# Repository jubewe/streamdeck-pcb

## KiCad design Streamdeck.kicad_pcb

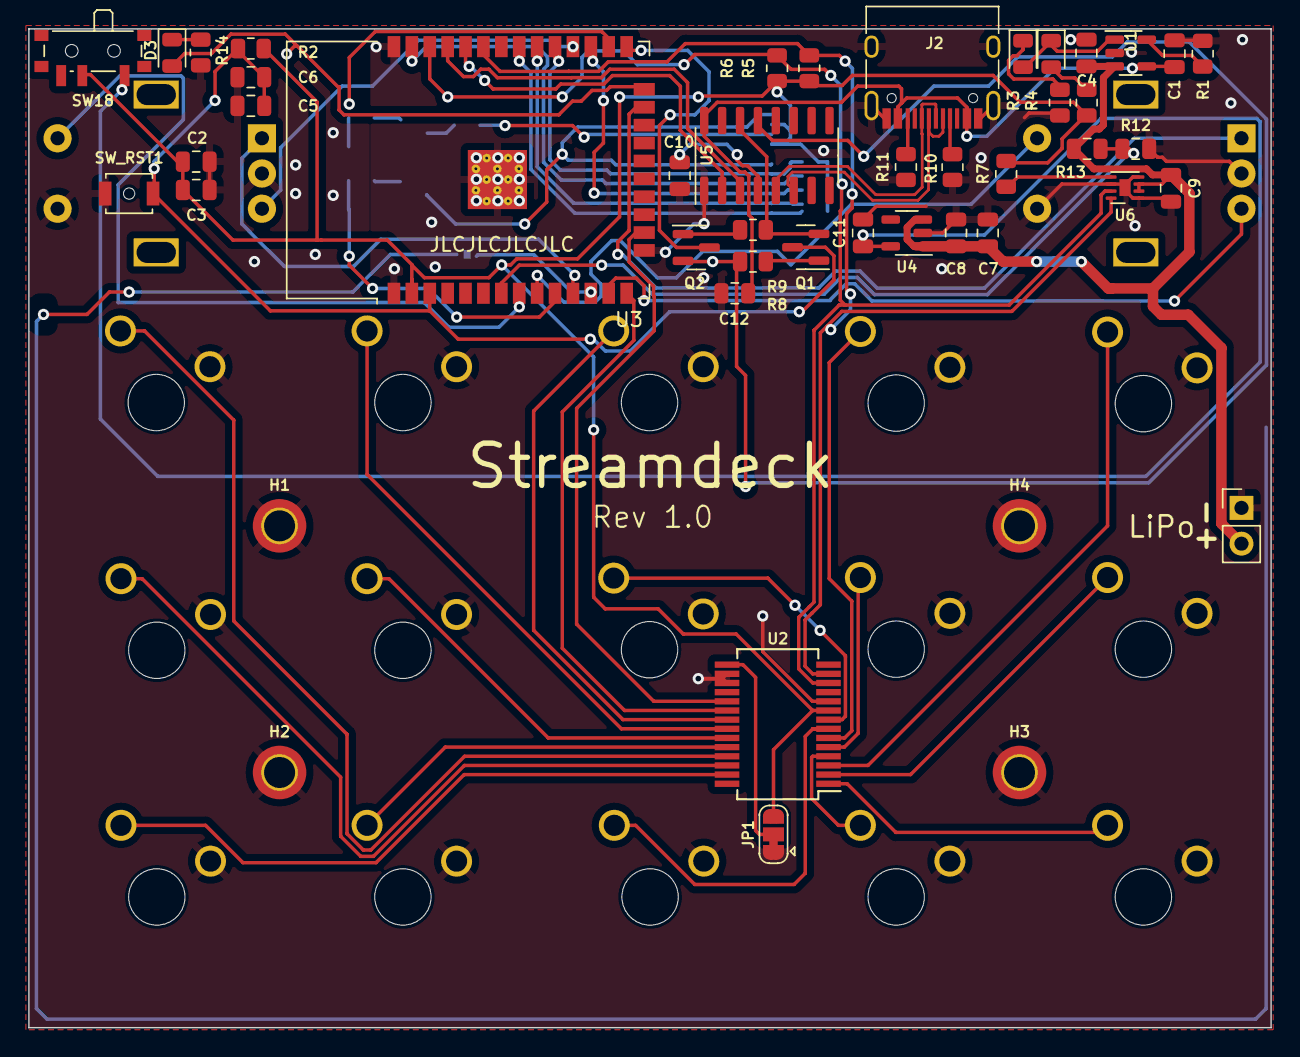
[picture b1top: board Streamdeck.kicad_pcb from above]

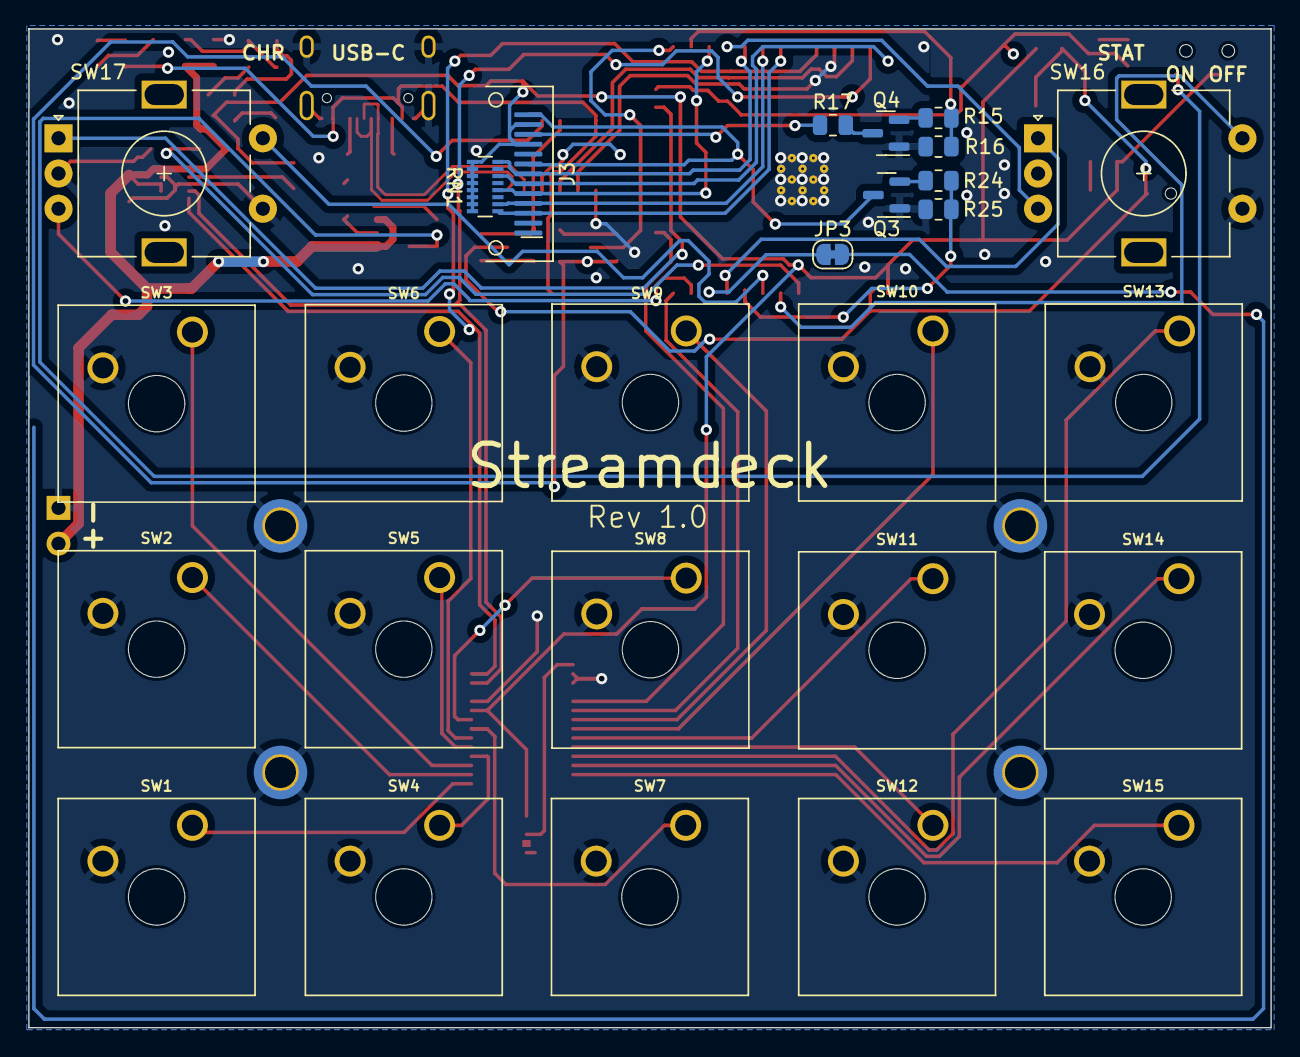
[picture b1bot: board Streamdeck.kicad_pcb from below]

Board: 2 copper layers, 88.1 x 70.9 mm, 73 parts (27 on the bottom side), 65 nets.

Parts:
C1, C2, C4, C7: 10µF; C_0805_2012Metric
C3, C6, C9, C10, C12: 0.1µF; C_0805_2012Metric
C5, C8, C11: 1µF; C_0805_2012Metric
D1: LED_GREEN; LED_0805_2012Metric
D2: LED_RED; LED_0805_2012Metric
D3: LED_BLUE; LED_0805_2012Metric
H1, H2, H3, H4: MountingHole_Pad; MountingHole_2.2mm_M2_DIN965_Pad_TopBottom
J1: Conn_01x02_Socket; PinHeader_1x02_P2.54mm_Vertical
J2: XUNPU_TYPEC-304J-BCP16; XUNPU TYPEC-304J-BCP16
J3: Conn_01x13_Pin; ST7789 LCD TFT
JP1: Jumper_3_Bridged12; SolderJumper-3_P1.3mm_Bridged12_RoundedPad1.0x1.5mm
JP3: Jumper_2_Bridged; SolderJumper-2_P1.3mm_Bridged_RoundedPad1.0x1.5mm
Q1, Q2: BC817; SOT-23
Q3, Q4: S8050; SOT-23
R1, R3, R4, R14: 2k; R_0805_2012Metric
R2, R8, R9: 10k; R_0805_2012Metric
R5, R6: 2k2; R_0805_2012Metric
R7: 4.7k; R_0805_2012Metric
R10, R11: 5.1k; R_0805_2012Metric
R12, R13: R; C_0805_2012Metric
R15, R24: 1k; R_0805_2012Metric
R16, R25: 100k; R_0805_2012Metric
R17: 36; R_0805_2012Metric
RN1: R_Pack08; R_Array_Convex_8x0602
SW1, SW2, SW3, SW4, SW5, SW6, SW7, SW8, SW9, SW10, SW11, SW12, SW13, SW14, SW15: SW; SW_Cherry_MX_1.00u_Plate_Custom
SW16, SW17: RotaryEncoder_Switch; RotaryEncoder_Alps_EC11E-Switch_Vertical_H20mm
SW18: SW_SPST; SW_SPDT_PCM12
SW_RST1: SW_RESET; SW_SPST_B3U-1000P-B
U1: MCP73831-2-OT; SOT-23-5
U2: MCP23017_SO; SSOP-28_5.3x10.2mm_P0.65mm
U3: ESP32-WROOM-32
U4: XC6220B331MR; SOT-23-5
U5: CH340C; SOIC-16_3.9x9.9mm_P1.27mm
U6: MAX17048; TDFN-8-1EP_2x2mm_P0.5mm_EP0.8x1.2mm

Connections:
+3.3V: C2.1, C3.1, J3.10, J3.12, JP1.3 (B), R2.2, R4.2, R5.1, R6.1, R7.2, RN1.9 (R8.2), RN1.10 (R7.2), RN1.11 (R6.2), RN1.12 (R5.2), RN1.13 (R4.2), RN1.14 (R3.2), RN1.15 (R2.2), RN1.16 (R1.2), SW18.2 (B), U2.9 (VDD), U3.2 (VDD)
+5V: C1.1, C12.2, J2.A4 (VBUS), J2.B4 (VBUS), U1.4 (V_{DD}), U5.16 (VCC)
+BATT: C4.2, C7.1, C8.1, C9.1, J1.2, R13.1, U1.3 (V_{BAT}), U4.1 (VIN), U4.3 (CE), U6.2 (CELL), U6.3 (VDD)
-BATT: C1.2, C2.2, C3.2, C4.1, C5.1, C6.1, C7.2, C8.2, C9.2, C10.1, C11.2, C12.1, H1.1, H2.1, H3.1, H4.1, J1.1, J2.13 (SHLD), J2.14 (SHLD), J2.15 (SHLD), J2.16 (SHLD), J2.A1 (GND), J2.B1 (GND), JP1.1 (A), Q3.1 (E), Q4.1 (E), R1.1, R3.2, R10.1, R11.1, R12.2, R14.2, R16.2, R25.2, SW1.2, SW2.2, SW3.2, SW4.2, SW5.2, SW6.2, SW7.2, SW8.2, SW9.2, SW10.2, SW11.2, SW12.2, SW13.2, SW14.2, SW15.2, SW16.C, SW16.S1, SW17.C, SW17.S1, SW_RST1.1, U1.2 (V_{SS}), U2.10 (VSS), U2.16 (A1), U2.17 (A2), U3.1 (GND), U3.15 (GND), U3.38 (GND), U3.39 (GND), U4.2 (GND), U5.1 (GND), U6.1 (CTG), U6.4 (GND), U6.6 (QSTRT), U6.9 (PAD)
CHRG_STAT: D1.2 (A), D2.1 (K), U1.1 (STAT)
DN: J2.A7 (DN1), J2.B7 (DN2), U5.6 (UD-)
DP: J2.A6 (DP1), J2.B6 (DP2), U5.5 (UD+)
ENC_A_1: SW16.A, U3.11 (IO26)
ENC_A_2: SW17.A, U3.23 (IO15)
ENC_B_1: SW16.B, U3.28 (IO17)
ENC_B_2: SW17.B, U3.13 (IO14)
ENC_SW_1: SW16.S2, U3.8 (IO32)
ENC_SW_2: SW17.S2, U3.9 (IO33)
ESP_EN: C5.2, C6.2, Q1.3 (C), R2.1, SW_RST1.2, U3.3 (EN)
ESP_IO0: Q2.3 (C), U3.25 (IO0)
ESP_RXD: U3.34 (RXD0/IO3), U5.2 (TXD)
ESP_TXD: U3.35 (TXD0/IO1), U5.3 (RXD)
INT_A: U2.20 (INTA), U3.14 (IO12)
INT_B: U2.19 (INTB), U3.16 (IO13)
LED_STAT: D3.2 (A), U3.24 (IO2)
unnamed: D1.1 (K), R3.1
unnamed: D2.2 (A), R4.1
unnamed: D3.1 (K), R14.1
unnamed: J2.A5 (CC1), R10.2
unnamed: J2.B5 (CC2), R11.2
unnamed: J3.8, J3.13, Q3.3 (C)
unnamed: JP1.2 (C), U2.15 (A0)
unnamed: JP3.1 (A), U3.12 (IO27)
unnamed: Q1.1 (B), R8.2
unnamed: Q1.2 (E), R9.1, U5.14 (~RTS)
unnamed: Q2.1 (B), R9.2
unnamed: Q2.2 (E), R8.1, U5.13 (~DTR)
unnamed: Q3.2 (B), R24.1
unnamed: Q4.2 (B), R15.1
unnamed: Q4.3 (C), R17.2
unnamed: C11.1, SW18.1 (A), U4.5 (VOUT)
unnamed: R1.2, U1.5 (PROG)
unnamed: SW9.1, U2.21 (GPA0)
unnamed: SW10.1, U2.22 (GPA1)
unnamed: SW11.1, U2.23 (GPA2)
unnamed: SW12.1, U2.24 (GPA3)
unnamed: SW13.1, U2.25 (GPA4)
unnamed: SW14.1, U2.26 (GPA5)
unnamed: SW15.1, U2.27 (GPA6)
unnamed: SW1.1, U2.1 (GPB0)
unnamed: SW2.1, U2.2 (GPB1)
unnamed: SW3.1, U2.3 (GPB2)
unnamed: SW4.1, U2.4 (GPB3)
unnamed: SW5.1, U2.5 (GPB4)
unnamed: SW6.1, U2.6 (GPB5)
unnamed: SW7.1, U2.7 (GPB6)
unnamed: SW8.1, U2.8 (GPB7)
unnamed: R12.1, R13.2, U3.7 (IO35)
unnamed: C10.2, U5.4 (V3)
unnamed: R7.1, U6.5 (ALRT)
SCL: R6.2, U2.12 (SCK), U3.36 (IO22), U6.7 (SCL)
SDA: R5.2, U2.13 (SDA), U3.33 (IO21), U6.8 (SDA)
TFT_CS: J3.7, RN1.8 (R8.1), U3.29 (IO5)
TFT_EN: R24.2, R25.1, U3.10 (IO25)
TFT_LED: R15.2, R16.1, U3.26 (IO4)
TFT_LEDK: J3.11, R17.1
TFT_RES: J3.6, RN1.6 (R6.1), U3.37 (IO23)
TFT_RS: J3.5, RN1.4 (R4.1), U3.27 (IO16)
TFT_SCL: J3.4, RN1.2 (R2.1), U3.30 (IO18)
TFT_SDA: J3.3, RN1.1 (R1.1), U3.31 (IO19)

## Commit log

2023-05-26 v0.0.1
2023-05-26 pcb-0.0.2
2023-05-26 v0.0.3
2023-05-26 v0.0.4
2023-05-26 v0.0.5
2023-05-27 v0.0.6
2023-05-28 v0.0.7
2023-07-28 v0.0.8
